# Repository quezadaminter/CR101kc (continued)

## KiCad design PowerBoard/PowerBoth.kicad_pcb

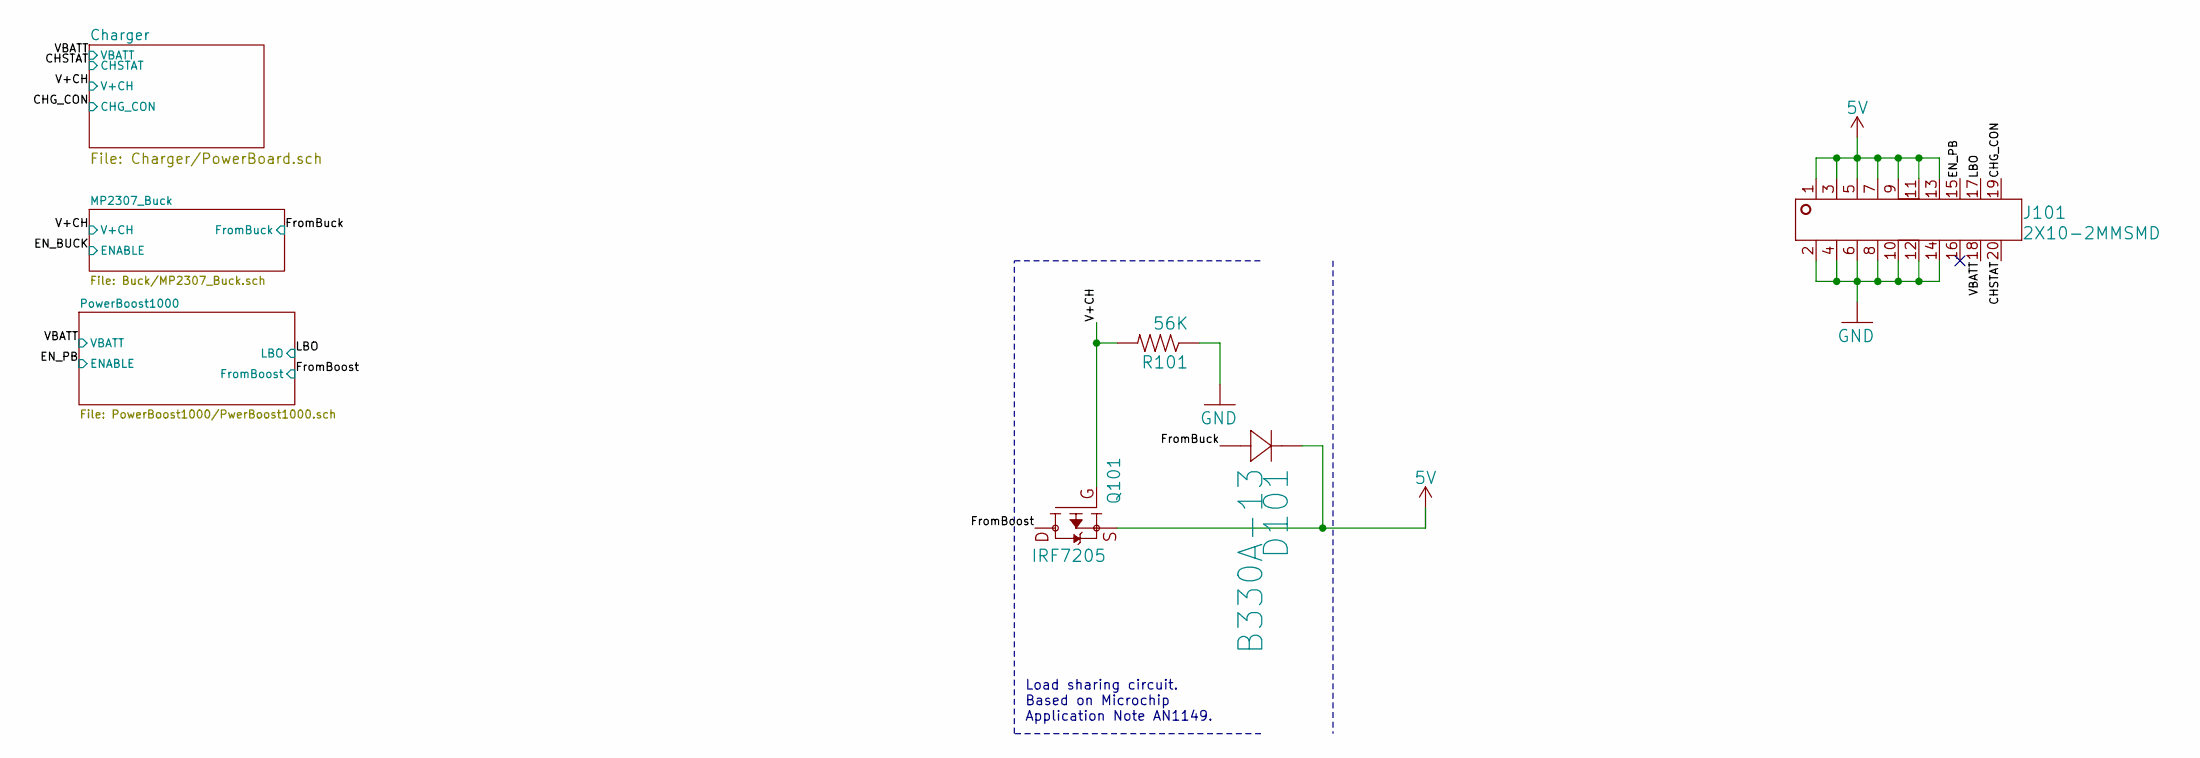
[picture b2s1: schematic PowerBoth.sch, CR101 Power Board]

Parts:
D101: B330A-13; SMA-M; DigiKey B330B-13-F
J101: 2X10-2MMSMD; 2X10-2MM; DigiKey NPPN102GFNP-RC
Q101: IRF7205; 8SOIC; LCSC Part Number C55419
R101: 56K; 1206; DigiKey CRCW120656K0FKEA

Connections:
5V: D101.1, J101.1, J101.3, J101.5, J101.7, J101.9, J101.11, J101.13, Q101.1 (S), Q101.2 (S), Q101.3 (S)
/CHG_CON: J101.19; also elsewhere on the board
/CHSTAT: J101.20; also elsewhere on the board
/EN_PB: J101.15; also elsewhere on the board
/FromBoost: Q101.5 (D), Q101.6 (D), Q101.7 (D), Q101.8 (D); also elsewhere on the board
/FromBuck: D101.2; also elsewhere on the board
/LBO: J101.17; also elsewhere on the board
/V+CH: Q101.4 (G), R101.2; also elsewhere on the board
/VBATT: J101.18; also elsewhere on the board
GND: J101.2, J101.4, J101.6, J101.8, J101.10, J101.12, J101.14, R101.1; also elsewhere on the board

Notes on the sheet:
Load sharing circuit. Based on Microchip Application Note AN1149.

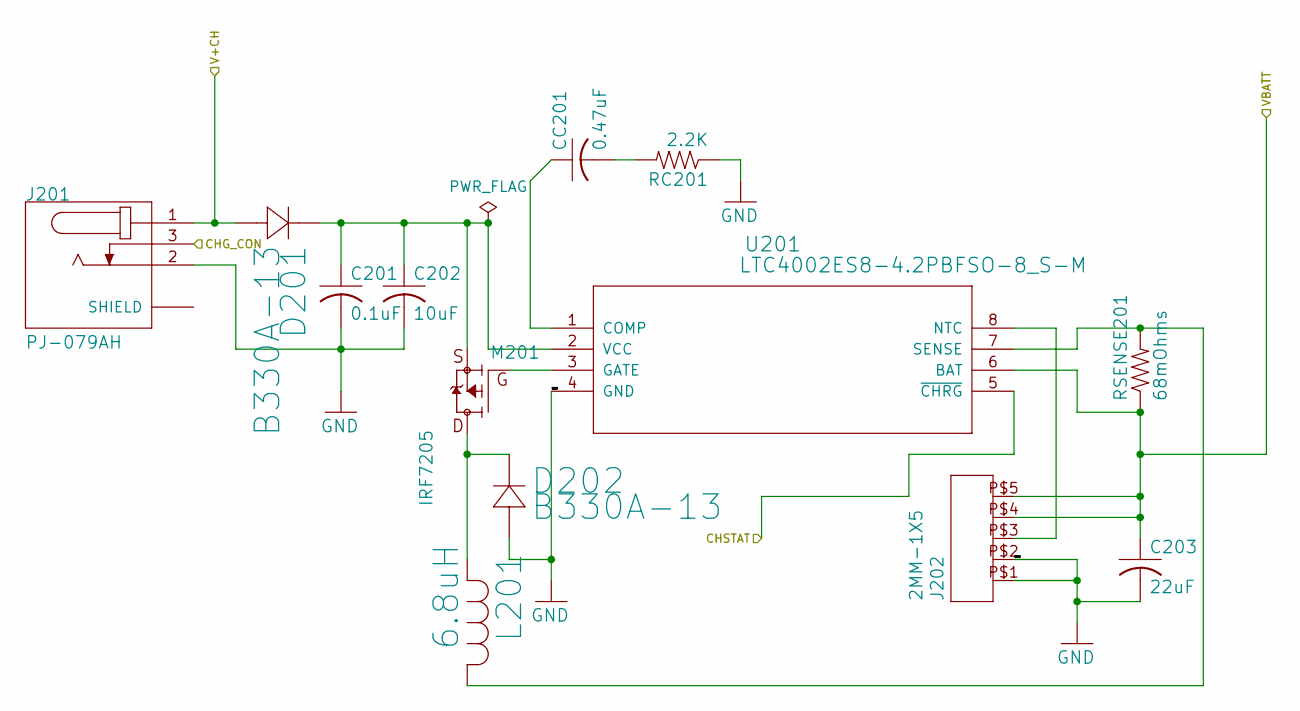
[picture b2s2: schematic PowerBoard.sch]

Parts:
C201: 0.1uF; C_0805_2012Metric_Pad1.15x1.40mm_HandSolder; LCSC Part Number C49678
C202: 10uF; C_0805_2012Metric_Pad1.15x1.40mm_HandSolder; DigiKey EMK212BB7106MG-T
C203: 22uF; C_1210_3225Metric_Pad1.42x2.65mm_HandSolder; DigiKey CL21A226MAQNNNE
CC201: 0.47uF; C_0603_1608Metric_Pad1.05x0.95mm_HandSolder; DigiKey C0805C474K3RACAUTO
D201, D202: B330A-13; SMA-M; DigiKey B330B-13-F
J201: PJ-079AH; CUI_PJ-079AH; DigiKey PJ-079AH
J202: 2MM-1X5; 2MM_1X5; DigiKey 0533250560
L201: 6.8uH; IND_B952AS-H-220M=P3; DigiKey #B952AS-H-6R8N=P3
M201: IRF7205; 8SOIC; LCSC Part Number C55419
RC201: 2.2K; R1206; DigiKey RC0805FR-072K2L
RSENSE201: 68mOhms; R1206; DigiKey KDV08FR068ET
U201: LTC4002ES8-4.2PBFSO-8_S-M; SO-8_S-M; DigiKey LTC4002ES8-4.2#TRPBF

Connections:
/CHG_CON: J201.3; also elsewhere on the board
/CHSTAT: U201.5 (~CHRG); also elsewhere on the board
/V+CH: D201.2, J201.1; also elsewhere on the board
/VBATT: C203.1, J202.P$4, J202.P$5, RSENSE201.1, U201.6 (BAT); also elsewhere on the board
GND: C201.2, C202.2, C203.2, D202.2, J201.2, J202.P$1, J202.P$2, RC201.1, U201.4 (GND); also elsewhere on the board
unnamed: C201.1, C202.1, D201.1, M201.1 (S), M201.2 (S), M201.3 (S), U201.2 (VCC)
unnamed: CC201.1, U201.1 (COMP)
unnamed: CC201.2, RC201.2
unnamed: D202.1, L201.2, M201.5 (D), M201.6 (D), M201.7 (D), M201.8 (D)
unnamed: J201.S1 (SHIELD), J201.S2 (SHIELD)
unnamed: J202.P$3, U201.8 (NTC)
unnamed: L201.1, RSENSE201.2, U201.7 (SENSE)
unnamed: M201.4 (G), U201.3 (GATE)

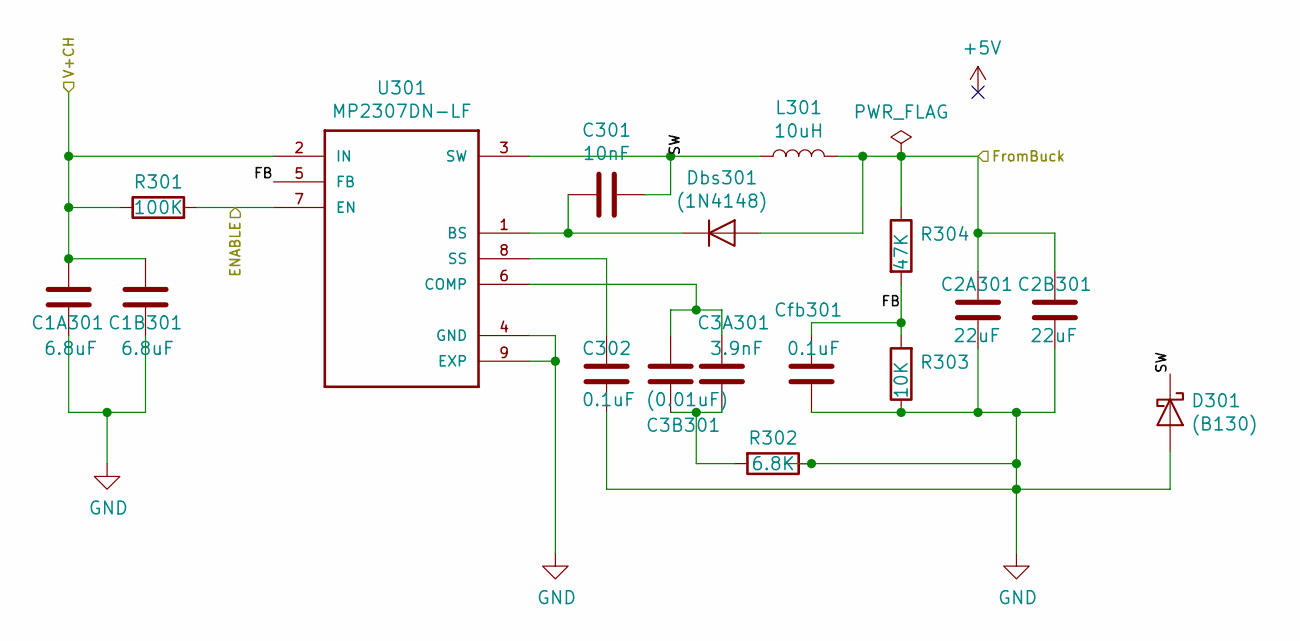
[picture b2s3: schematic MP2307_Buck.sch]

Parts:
C1A301, C1B301: 6.8uF; C_0805_2012Metric_Pad1.15x1.40mm_HandSolder; DigiKey C2012X5R1C685M085AC
C2A301, C2B301: 22uF; C_0805_2012Metric_Pad1.15x1.40mm_HandSolder; DigiKey EMK212BB7106MG-T
C3A301: 3.9nF; C_0805_2012Metric_Pad1.15x1.40mm_HandSolder; DigiKey C0805C395K8PACTU
C3B301: (0.01uF); C_0805_2012Metric_Pad1.15x1.40mm_HandSolder; DigiKey C0805C103K3RACTU
C301: 10nF; C_0805_2012Metric_Pad1.15x1.40mm_HandSolder; DigiKey C0805C104M3RACTU
C302: 0.1uF; C_0805_2012Metric_Pad1.15x1.40mm_HandSolder; DigiKey C0805C104M3RACTU
Cfb301: 0.1uF; C_0805_2012Metric_Pad1.15x1.40mm_HandSolder; DigiKey C0805C104M3RACTU
D301: (B130); D_SMB_Handsoldering; DigiKey B130LB-13-F
Dbs301: (1N4148); D_SOD-123; DigiKey 1N4148WQ-7-F
L301: 10uH; L_10.4x10.4_H4.8; DigiKey SD8350-100-R
R301: 100K; R_0805_2012Metric_Pad1.15x1.40mm_HandSolder; DigiKey RC0805FR-07100KL
R302: 6.8K; R_0805_2012Metric_Pad1.15x1.40mm_HandSolder; DigiKey CRG0805F6K8
R303: 10K; R_0805_2012Metric_Pad1.15x1.40mm_HandSolder; DigiKey RC0805FR-0710KL
R304: 47K; R_0805_2012Metric_Pad1.15x1.40mm_HandSolder; DigiKey RC0805FR-0747KL
U301: MP2307DN-LF; SOIC127P600X170-9N; DigiKey MP2307DN-LF-Z

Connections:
/EN_BUCK: R301.2, U301.7 (EN)
/FromBuck: C2A301.1, C2B301.1, Dbs301.2 (A), L301.2, R304.1; also elsewhere on the board
/MP2307_Buck/FB: Cfb301.1, R303.2, R304.2, U301.5 (FB)
/MP2307_Buck/SW: C301.1, D301.1 (K), L301.1, U301.3 (SW)
/V+CH: C1A301.1, C1B301.1, R301.1, U301.2 (IN); also elsewhere on the board
GND: C1A301.2, C1B301.2, C2A301.2, C2B301.2, C302.2, Cfb301.2, D301.2 (A), R302.1, R303.1, U301.4 (GND), U301.9 (EXP); also elsewhere on the board
unnamed: C3A301.1, C3B301.1, U301.6 (COMP)
unnamed: C3A301.2, C3B301.2, R302.2
unnamed: C301.2, Dbs301.1 (K), U301.1 (BS)
unnamed: C302.1, U301.8 (SS)

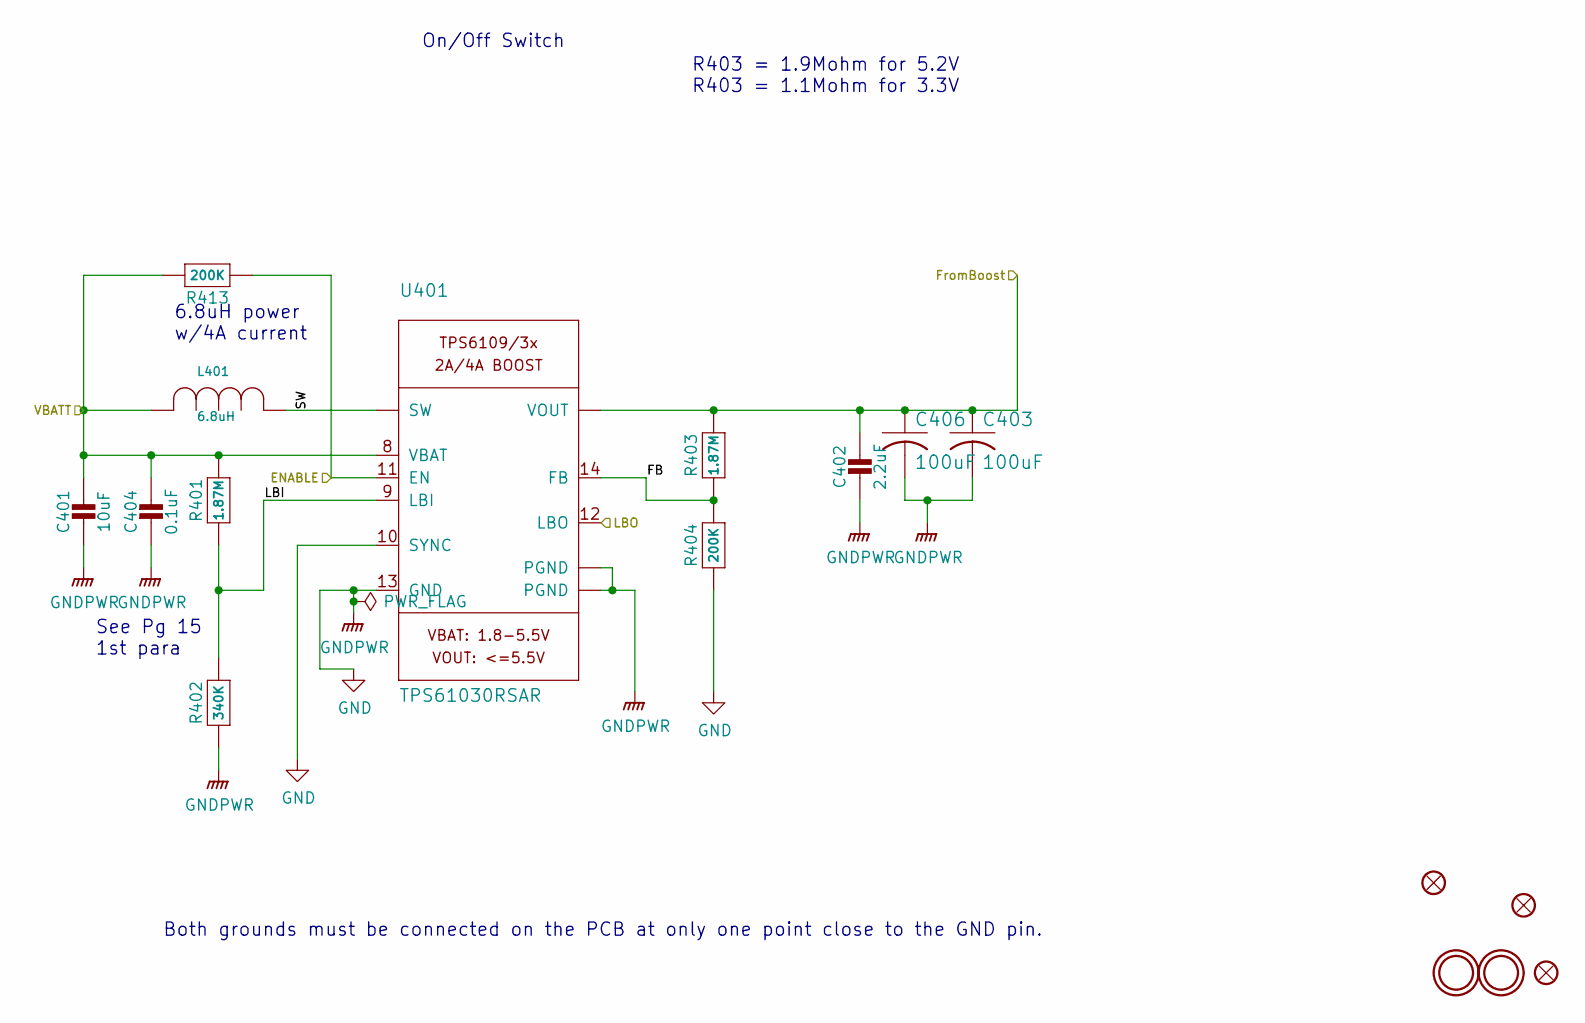
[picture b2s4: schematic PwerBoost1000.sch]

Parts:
C401: 10uF; C_0805_2012Metric_Pad1.15x1.40mm_HandSolder; DigiKey EMK212BB7106MG-T
C402: 2.2uF; C_0805_2012Metric_Pad1.15x1.40mm_HandSolder; DigiKey GRM21BR71C225KA12L
C403, C406: 100uF; C_1210_3225Metric_Pad1.42x2.65mm_HandSolder; DigiKey EMK325ABJ107MM-T
C404: 0.1uF; C_0805_2012Metric_Pad1.15x1.40mm_HandSolder; DigiKey C0805C104M3RACTU
FID401, FID402, FID403: FIDUCIAL\"\"; FIDUCIAL_1MM
L401: 6.8uH; IND_B952AS-H-220M=P3; DigiKey #B952AS-H-6R8N=P3
R401, R403: 1.87M; R_0805_2012Metric_Pad1.15x1.40mm_HandSolder; DigiKey ERJ-6ENF1874V
R402: 340K; R_0805_2012Metric_Pad1.15x1.40mm_HandSolder; DigiKey RC0805FR-07340KL
R404, R413: 200K; R_0805_2012Metric_Pad1.15x1.40mm_HandSolder; DigiKey RMCF0805FT200K
U401: TPS61030RSAR; PVQFN-16; DigiKey TPS61030RSAR
U$401, U$402: MOUNTINGHOLE2.5; MountingHole_2.5mm_Pad

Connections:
/EN_PB: R413.1, U401.11 (EN); also elsewhere on the board
/FromBoost: C402.1, C403.1, C406.1, R403.2, U401.1 (VOUT), U401.15 (VOUT), U401.16 (VOUT); also elsewhere on the board
/LBO: U401.12 (LBO); also elsewhere on the board
/PowerBoost1000/FB: R403.1, R404.2, U401.14 (FB)
/PowerBoost1000/LBI: R401.1, R402.2, U401.9 (LBI)
/PowerBoost1000/SW: L401.1, U401.3 (SW), U401.4 (SW)
/VBATT: C401.1, C404.1, L401.2, R401.2, R413.2, U401.8 (VBAT); also elsewhere on the board
GND: C401.2, C402.2, C403.2, C404.2, C406.2, R402.1, R404.1, U401.5 (PGND), U401.6 (PGND), U401.7 (PGND), U401.10 (SYNC), U401.13 (GND), U401.17 (PGND), U401.P$18 (PGND), U401.P$19 (PGND), U401.P$20 (PGND), U401.P$21 (PGND), U401.P$22 (PGND); also elsewhere on the board

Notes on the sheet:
Both grounds must be connected on the PCB at only one point close to the GND pin.
On/Off Switch
See Pg 15 1st para
6.8uH power w/4A current
R403 = 1.9Mohm for 5.2V R403 = 1.1Mohm for 3.3V

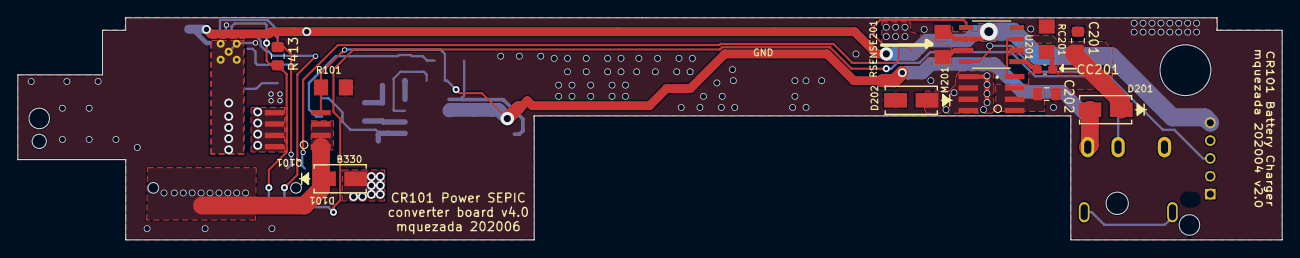
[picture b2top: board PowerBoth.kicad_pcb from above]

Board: 2 copper layers, 141.8 x 24.9 mm, 54 parts (0 on the bottom side), 28 nets.

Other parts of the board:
@HOLE0, @HOLE1, @HOLE2, @HOLE3, @HOLE4: (no value)

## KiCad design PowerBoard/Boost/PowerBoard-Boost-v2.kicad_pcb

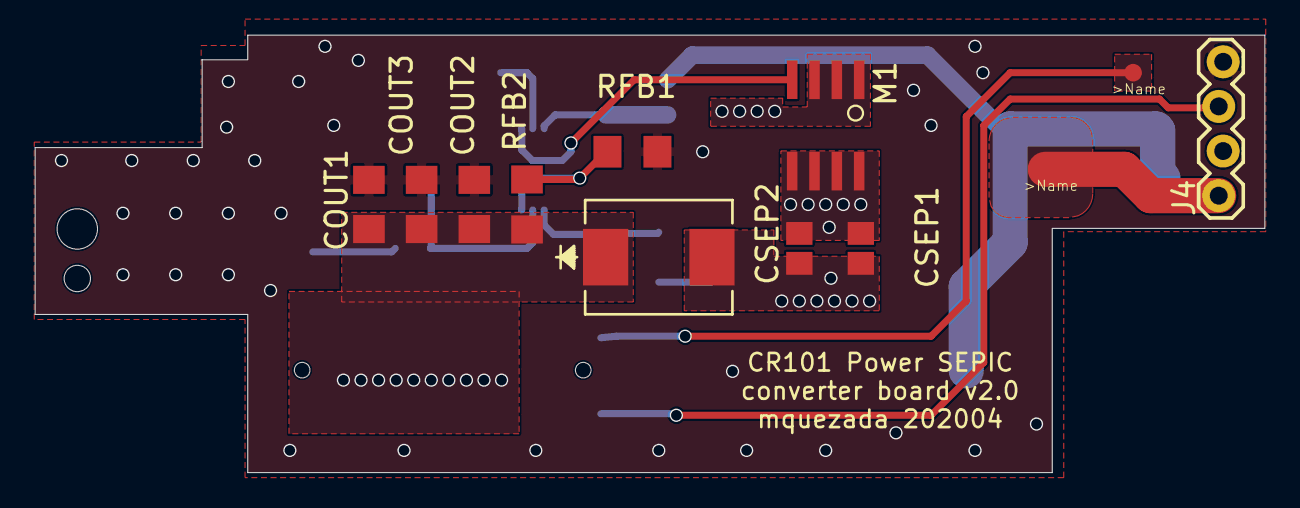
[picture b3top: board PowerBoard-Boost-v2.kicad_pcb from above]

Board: 2 copper layers, 70.0 x 24.9 mm, 28 parts (0 on the bottom side), 16 nets.

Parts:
@HOLE0, @HOLE1: (no value)
CBP1: 0.1uF; C1206
CCOMP1: 0.47uF; C1206
CCOMP2: 15nF; C0805
CFILT1: 1.5nF; C0805
CIN1, CIN2: 3.3uF; 153CLV-0505
COUT1, COUT2, COUT3: 47uF; C1206
CSEP1, CSEP2: 3.3uF; C0805
D1: SL44-E3_57TDIODE_DO214AB-M; DIODE_DO214AB-M
J1: 2X10-2MMSMD; 2X10-2MM
J4: CONN_04LOCK; 1X04_LOCK
L1: INDUCTOR_DUAL; DRQ125
M1: MOSFET_NSI4778DY; 8SOIC
RBP1: 20; R0805
RCOMP1: 215; R0805
RFADJ1: 76.8K; R0805
RFB1: 10k; R1206
RFB2: 29.4K; R1206
RFILT1: 100; R1206
RSENSE1: 0.009; R1206
TP1: Charger+; TEST_POINT_ROUND_1MM
TP2: STAT; TEST_POINT_ROUND_1MM
U1: LM3488QMM_NOPBDGK8-M; DGK8-M

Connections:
5V: COUT1.1, COUT2.1, COUT3.1, D1.1, J1.1, J1.3, J1.5, J1.7, J1.9, J1.11, J1.13, RFB2.2
/PowerBoard-Boost-v2_1/BB: CIN1.+, CIN2.+, J4.2, L1.1, RBP1.2
/PowerBoard-Boost-v2_1/COMP: CCOMP2.1, RCOMP1.2, U1.2
/PowerBoard-Boost-v2_1/DR: M1.4, U1.6
/PowerBoard-Boost-v2_1/FA: RFADJ1.2, U1.7
/PowerBoard-Boost-v2_1/FB: RFB1.2, RFB2.1, U1.3
/PowerBoard-Boost-v2_1/ISEN: CFILT1.1, RFILT1.2, U1.1
/PowerBoard-Boost-v2_1/SOURCE: M1.1, M1.2, M1.3, RFILT1.1, RSENSE1.2
/PowerBoard-Boost-v2_1/STAT: J1.20, TP2.1
/PowerBoard-Boost-v2_1/VCC_SENSE: J1.19, J4.3
/PowerBoard-Boost-v2_1/VIN: CBP1.1, RBP1.1, U1.8
/PowerBoard-Boost-v2_1/VIN3: CSEP1.2, CSEP2.2, L1.3, M1.5, M1.6, M1.7, M1.8
/PowerBoard-Boost-v2_1/VOUT: CSEP1.1, CSEP2.1, D1.2, L1.2
GND: CBP1.2, CCOMP1.2, CCOMP2.2, CFILT1.2, CIN1.-, CIN2.-, COUT1.2, COUT2.2, COUT3.2, J1.2, J1.4, J1.6, J1.8, J1.10, J1.12, J1.14, J1.16, J4.4, L1.4, RFADJ1.1, RFB1.1, RSENSE1.1, U1.4, U1.5
unnamed: CCOMP1.1, RCOMP1.1
VCC: J4.1, TP1.1

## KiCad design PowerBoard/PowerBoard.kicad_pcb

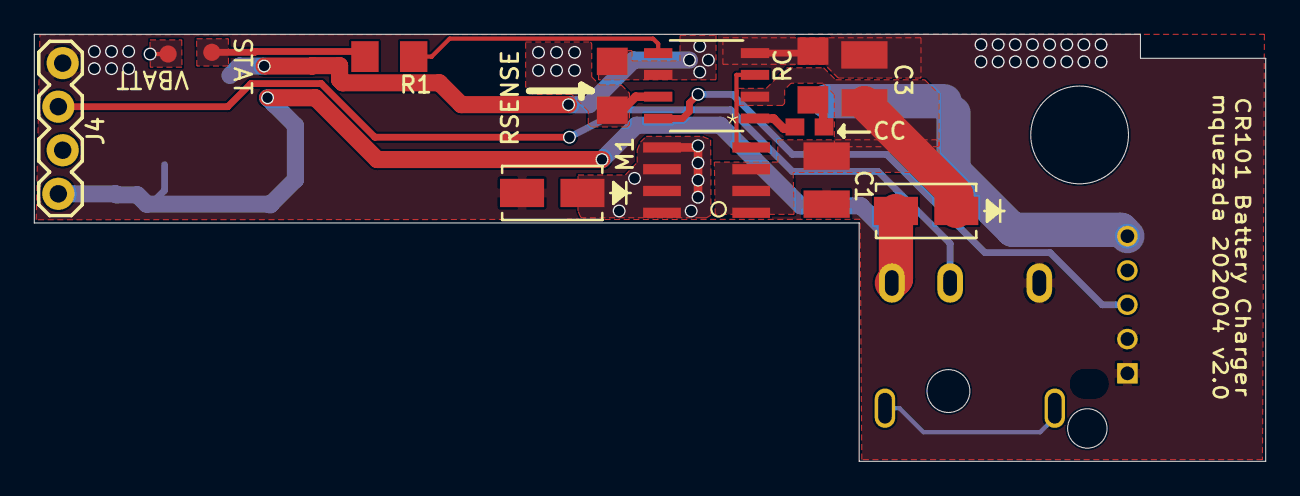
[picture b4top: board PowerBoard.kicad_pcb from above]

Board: 2 copper layers, 71.8 x 24.9 mm, 23 parts (0 on the bottom side), 15 nets.

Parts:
@HOLE0, @HOLE1, @HOLE2: (no value)
C1: 10uF; C1210
C2: 22uF; C1210
C3: 0.1uF; C1210
CC: 0.47uF; C0603
D1, D2, D3: B330A-13; SMA-M
J1: 2MM-1X5; 2MM_1X5
J2: PJ-079AH; CUI_PJ-079AH
J4: CONN_04LOCK; 1X04_LOCK
L1: 6.8uH; IND_B952AS-H-220M=P3
M1: IRF7205; 8SOIC
Q10: IRF7205; 8SOIC
R1: 2K; R1206
R47: 56K; 1206
RC: R-US_R1206; R1206
RSENSE: 68mOhms; R1206
TP1-STAT101: TEST_POINTROUND-1MM; TEST_POINT_ROUND_1MM
U1: LTC4002ES8-4.2PBFSO-8_S-M; SO-8_S-M
VBATT: TEST_POINTROUND-1MM; TEST_POINT_ROUND_1MM

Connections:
/STAT: R1.2, TP1-STAT101.1
/VCC_SENSE: J2.3, J4.3
GND: C1.2, C2.2, C3.2, D2.2, J1.P$1, J1.P$2, J2.2, J4.4, R47.1, RC.1, U1.4
unnamed: C1.1, C3.1, D1.1, M1.1, M1.2, M1.3, U1.2
unnamed: CC.1, U1.1
unnamed: CC.2, RC.2
unnamed: D2.1, L1.2, M1.5, M1.6, M1.7, M1.8
unnamed: D3.1, J4.2, Q10.1, Q10.2, Q10.3
unnamed: J1.P$3, U1.8
unnamed: J2.S1, J2.S2
unnamed: L1.1, RSENSE.2, U1.7
unnamed: M1.4, U1.3
unnamed: R1.1, U1.5
VCC: D1.2, D3.2, J2.1, J4.1, Q10.4, R47.2
V_BATT: C2.1, J1.P$4, J1.P$5, Q10.5, Q10.6, Q10.7, Q10.8, RSENSE.1, U1.6, VBATT.1

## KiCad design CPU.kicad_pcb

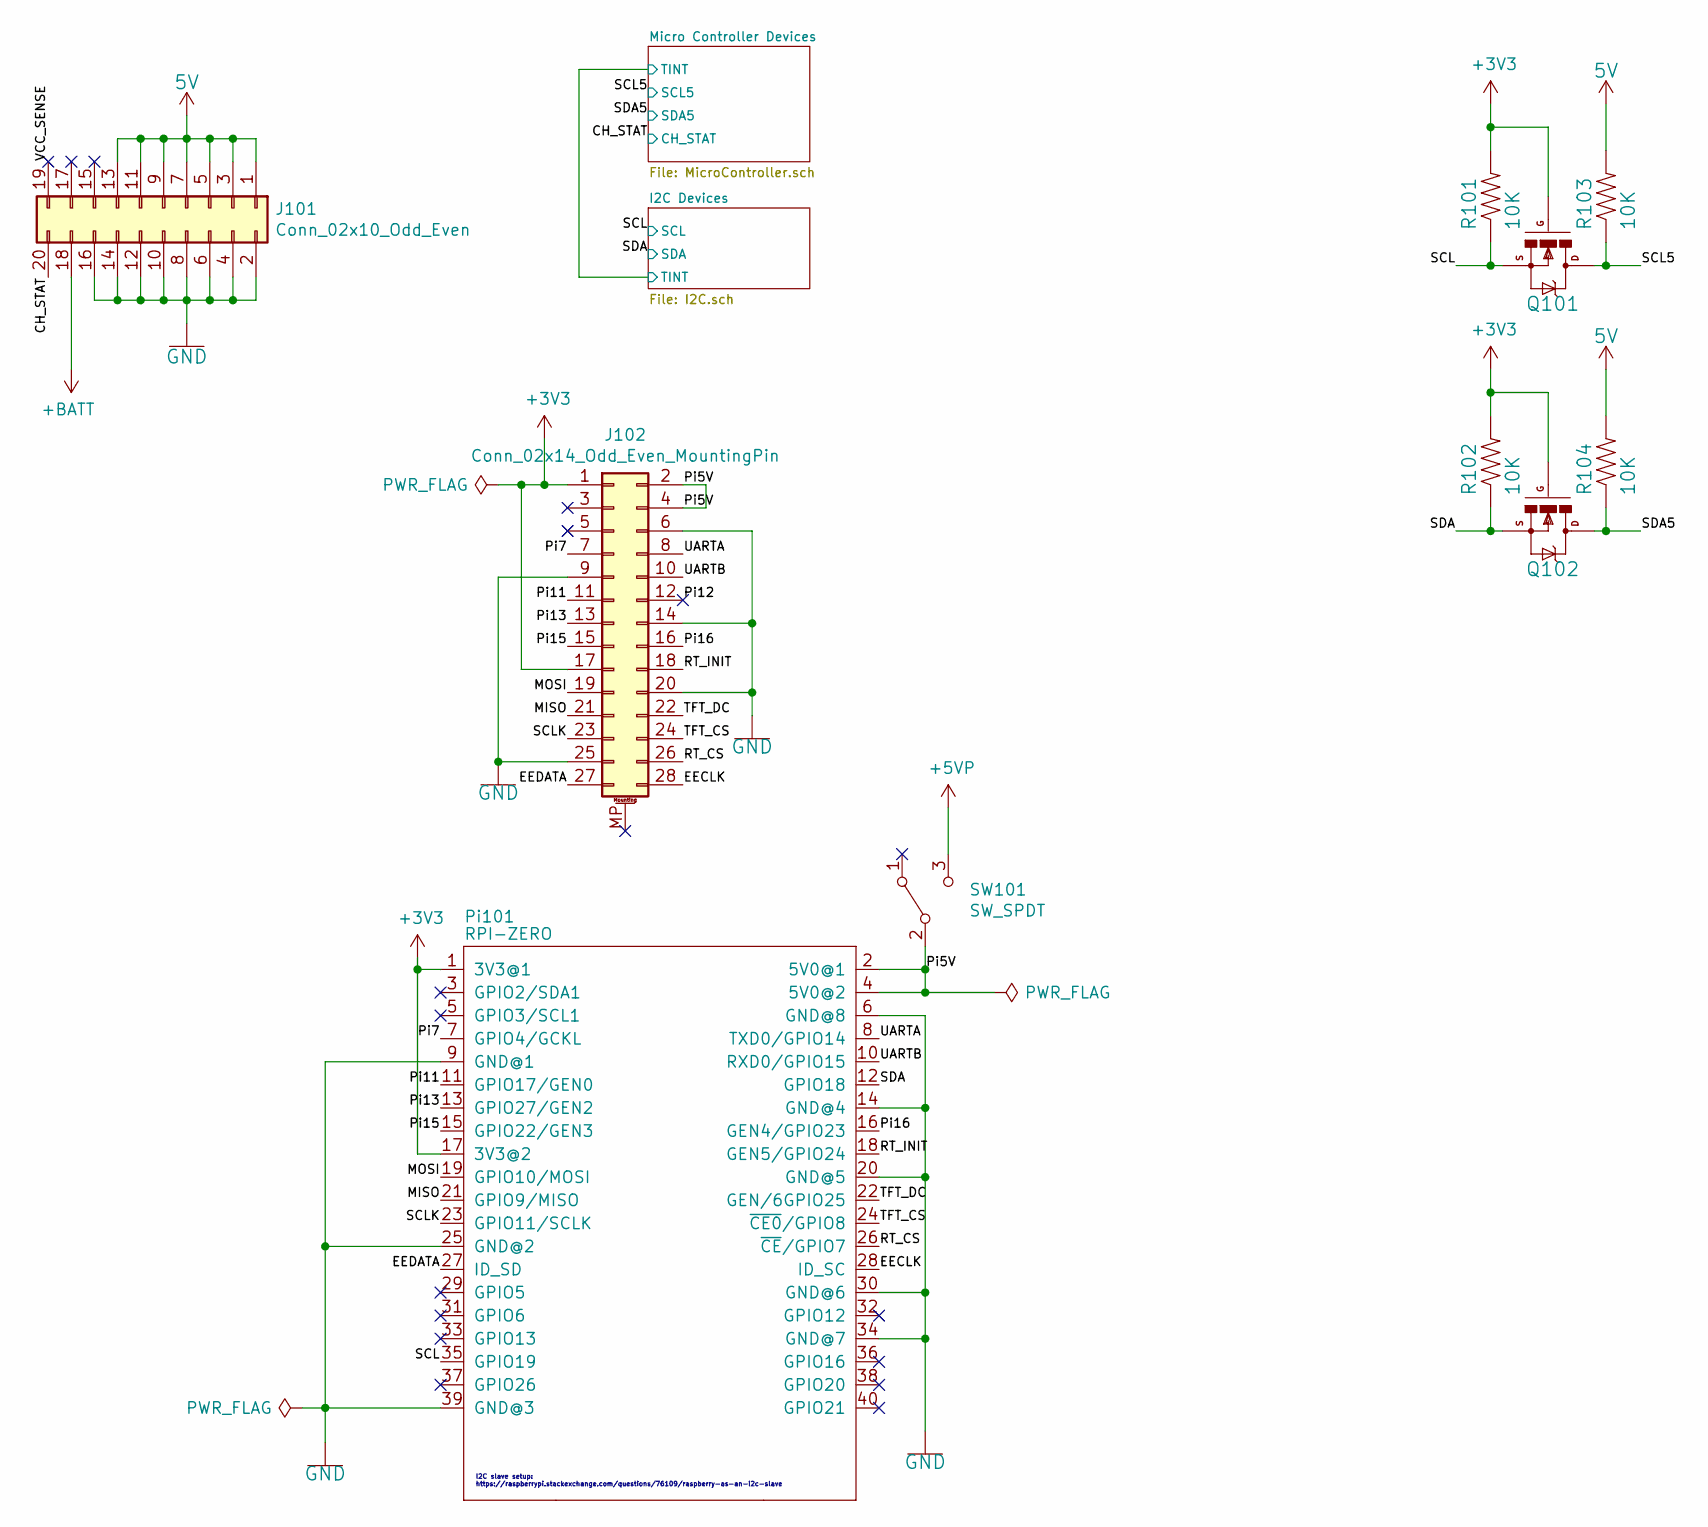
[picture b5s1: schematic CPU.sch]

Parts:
J101: Conn_02x10_Odd_Even; PinHeader_2x10_P2.00mm_Vertical_SMD; LCSC Part Number C135211
J102: Conn_02x14_Odd_Even_MountingPin; 2X14_SMT_MALE-2
Pi101: RPI-ZERO; RASPBERRYPI_Zero-No_Mounting_Holes
Q101, Q102: IRLML0040TR; SOT23; LCSC Part Number C67273
R101, R102, R103, R104: 10K; R1206; LCSC Part Number C17902
SW101: SW_SPDT; SWITCH_PCM12SMTR_SPDT; LCSC Part Number C221841

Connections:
5V: J101.1, J101.3, J101.5, J101.7, J101.9, J101.11, J101.13, R103.2, R104.2; also elsewhere on the board
+3V3: J102.1, J102.17, Pi101.1 (3V3@1), Pi101.17 (3V3@2), Q101.1 (G), Q102.1 (G), R101.2, R102.2; also elsewhere on the board
+5VP: SW101.3 (C); also elsewhere on the board
+BATT: J101.18; also elsewhere on the board
/CH_STAT: J101.20; also elsewhere on the board
/EECLK: J102.28, Pi101.28 (ID_SC)
/EEDATA: J102.27, Pi101.27 (ID_SD)
/MISO: J102.21, Pi101.21 (GPIO9/MISO)
/MOSI: J102.19, Pi101.19 (GPIO10/MOSI)
/Pi5V: J102.2, J102.4, Pi101.2 (5V0@1), Pi101.4 (5V0@2), SW101.2 (B)
/Pi7: J102.7, Pi101.7 (GPIO4/GCKL)
/Pi11: J102.11, Pi101.11 (GPIO17/GEN0)
/Pi12: J102.12
/Pi13: J102.13, Pi101.13 (GPIO27/GEN2)
/Pi15: J102.15, Pi101.15 (GPIO22/GEN3)
/Pi16: J102.16, Pi101.16 (GEN4/GPIO23)
/RT_CS: J102.26, Pi101.26 (~CE~/GPIO7)
/RT_INIT: J102.18, Pi101.18 (GEN5/GPIO24)
/SCL: Pi101.35 (GPIO19), Q101.2 (S), R101.1; also elsewhere on the board
/SCL5: Q101.3 (D), R103.1; also elsewhere on the board
/SCLK: J102.23, Pi101.23 (GPIO11/SCLK)
/SDA: Pi101.12 (GPIO18), Q102.2 (S), R102.1; also elsewhere on the board
/SDA5: Q102.3 (D), R104.1; also elsewhere on the board
/TFT_CS: J102.24, Pi101.24 (~CE0~/GPIO8)
/TFT_DC: J102.22, Pi101.22 (GEN/6GPIO25)
/UARTA: J102.8, Pi101.8 (TXD0/GPIO14)
/UARTB: J102.10, Pi101.10 (RXD0/GPIO15)
/VCC_SENSE: J101.19
GND: J101.2, J101.4, J101.6, J101.8, J101.10, J101.12, J101.14, J101.16, J102.6, J102.9, J102.14, J102.20, J102.25, Pi101.6 (GND@8), Pi101.9 (GND@1), Pi101.14 (GND@4), Pi101.20 (GND@5), Pi101.25 (GND@2), Pi101.30 (GND@6), Pi101.34 (GND@7), Pi101.39 (GND@3); also elsewhere on the board

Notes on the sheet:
I2C slave setup: https://raspberrypi.stackexchange.com/questions/76109/raspberry-as-an-i2c-slave

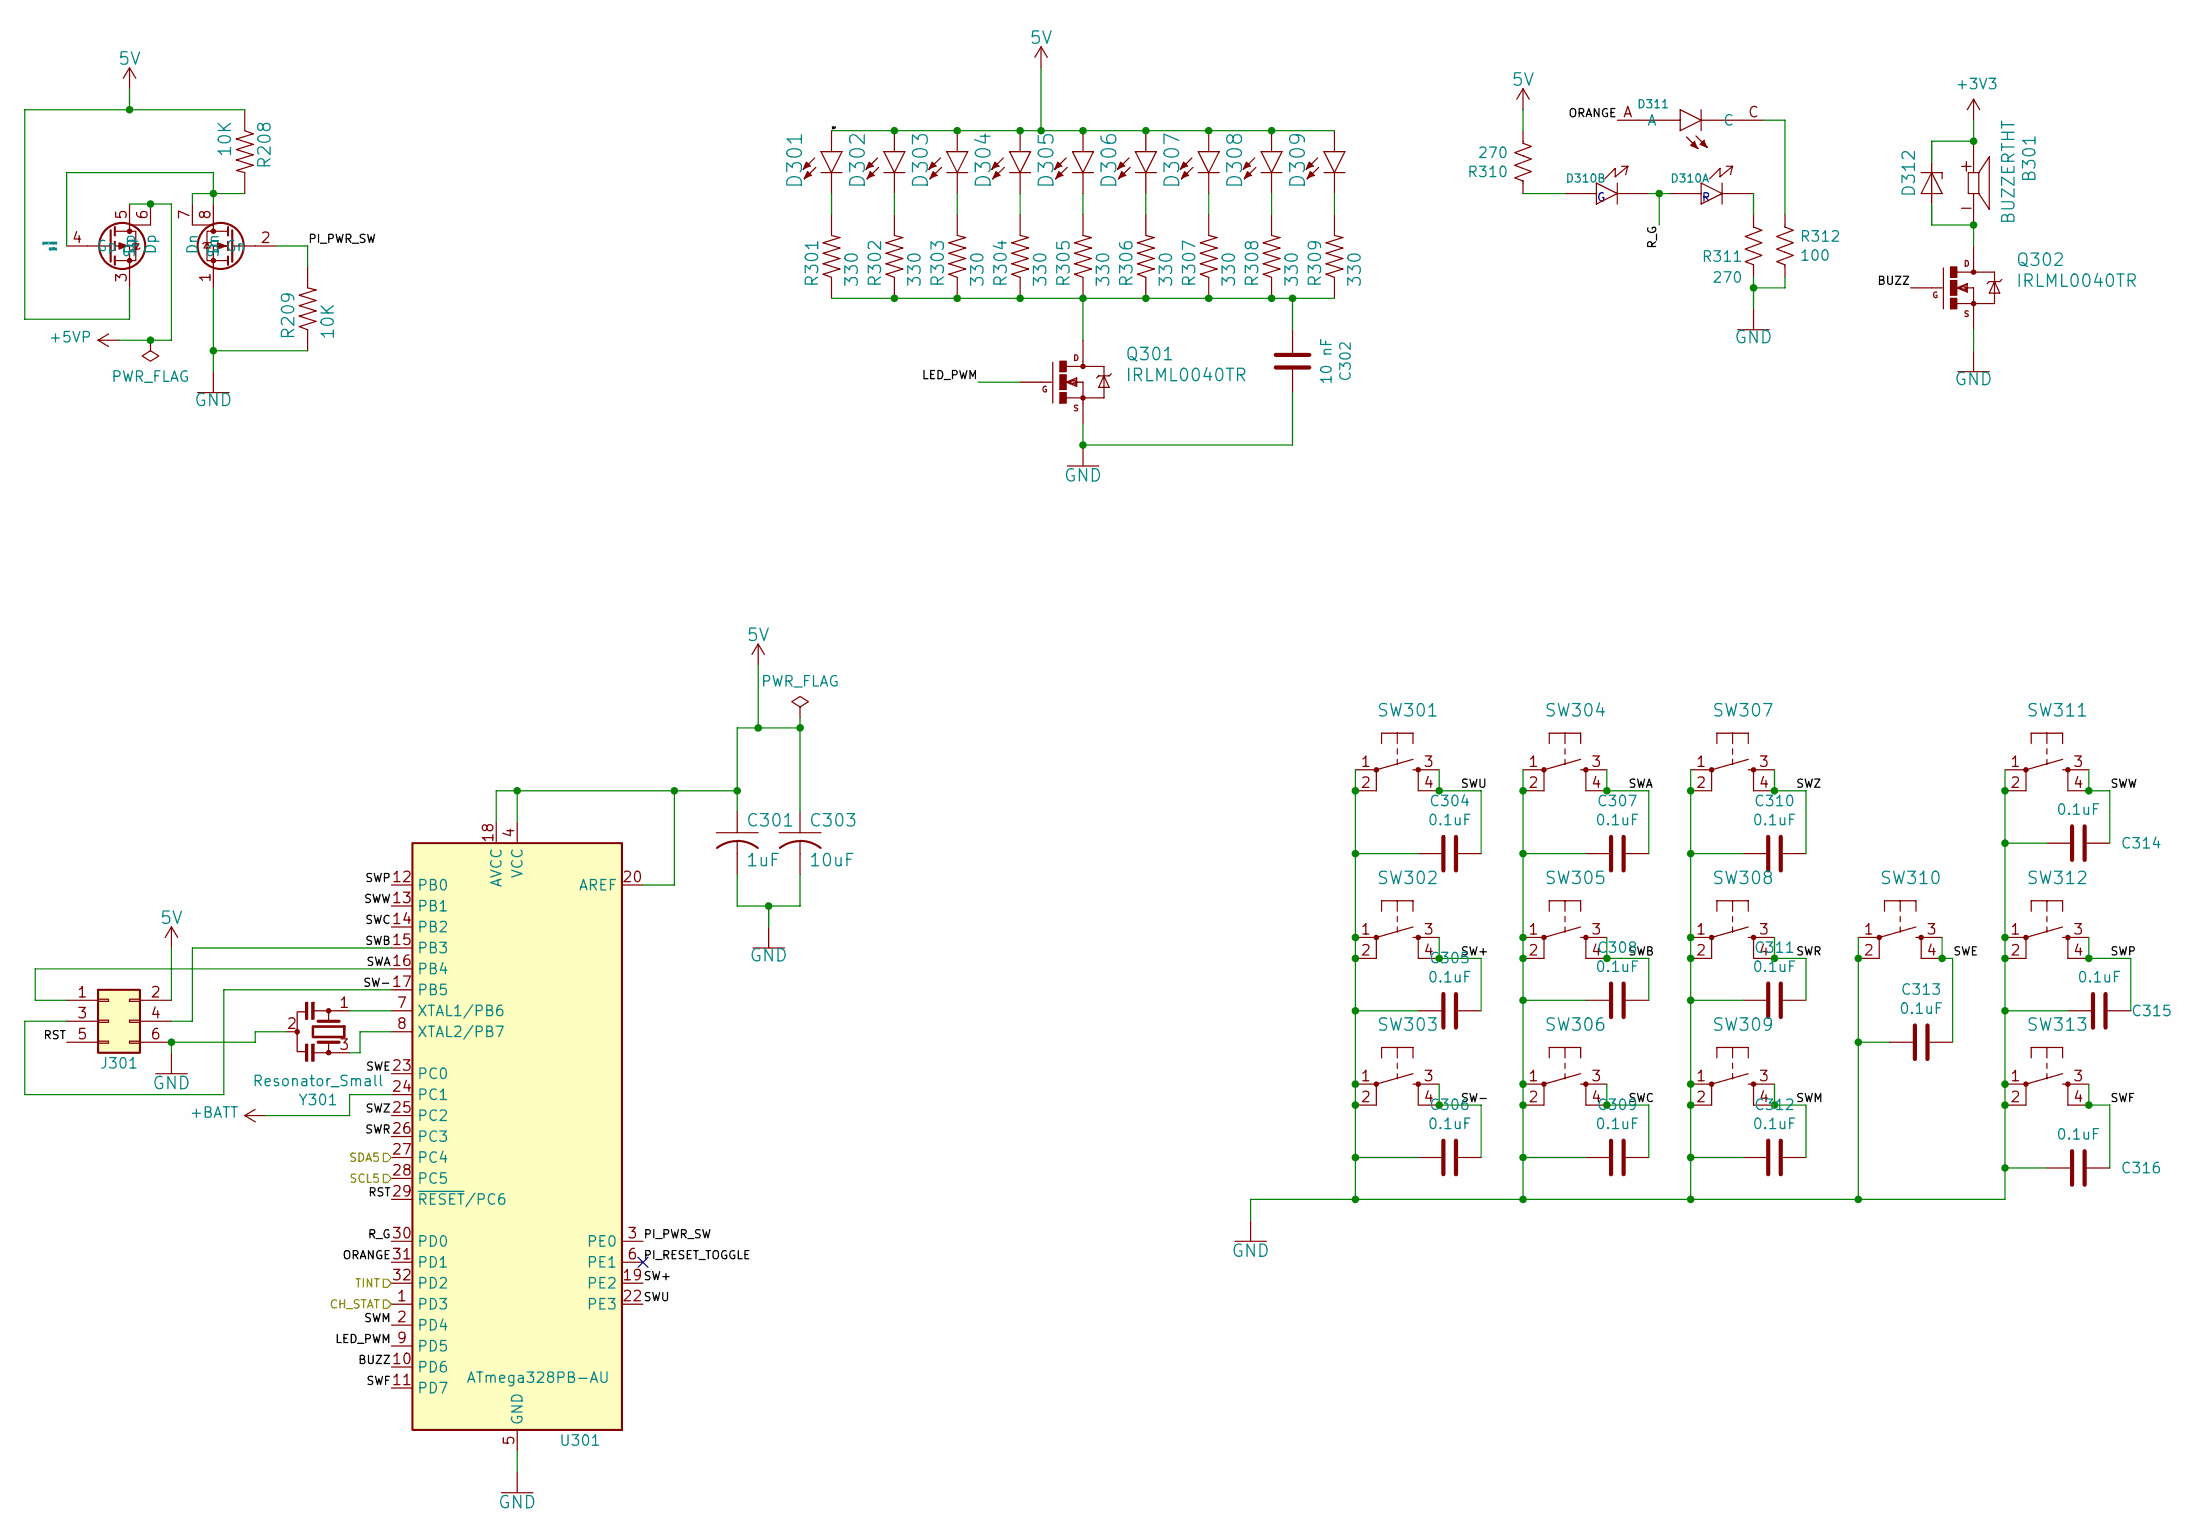
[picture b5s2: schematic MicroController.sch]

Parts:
B301: BUZZERTHT; XDCR_CMT-0904-85T; DigiKey CMT-0904-85T
C301: 1uF; C1210; LCSC Part Number C1848
C302: 10 nF; C_0805_2012Metric_Pad1.15x1.40mm_HandSolder; LCSC Part Number C1710
C303: 10uF; C1210; LCSC Part Number C13585
C304, C305, C306, C307, C308, C309, C310, C311, C312, C313, C314, C315, C316: 0.1uF; C_0805_2012Metric_Pad1.15x1.40mm_HandSolder; LCSC Part Number C49678
D301, D302, D303, D304, D305, D306, D307, D308, D309: LED0603; LED-0603; LCSC Part Number C161619
D310: RG; INOLUX_IN-S85DATRG; LCSC Part Number C391863
D311: 598-8030-107F; LEDSC160X80X70L45N; LCSC Part Number C264422
D312: DIODE; MICRO_SMP; LCSC Part Number C111315
J301: Conn_02x03_Odd_Even; PinHeader_2x03_P2.54mm_Vertical; DigiKey 818-22-006-10-002101, 818-22-006-10-005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
Q201: DMC4050; 8-SMD; DigiKey DMC4050SSD-13
Q301, Q302: IRLML0040TR; SOT23; LCSC Part Number C67273
R208, R209: 10K; R1206; LCSC Part Number C17902
R301, R302, R303, R304, R305, R306, R307, R308, R309: 330; R1206; LCSC Part Number C17930
R310, R311: 270; R_0805_2012Metric_Pad1.15x1.40mm_HandSolder; LCSC Part Number C17590
R312: 100; R_0805_2012Metric_Pad1.15x1.40mm_HandSolder; LCSC Part Number C17408
SW301, SW302, SW303, SW304, SW305, SW306, SW307, SW308, SW309, SW310, SW311, SW312, SW313: TACTILE_SWITCHPTS540-SMD; PTS540-ULTRA_LOW_PROFILE_SW_SPST; LCSC Part Number C221864
U301: ATmega328PB-AU; TQFP-32_7x7mm_P0.8mm
Y301: Resonator_Small; Resonator-3Pin_W7.0mm_H2.5mm; DigiKey CSTNE20M0VH3L000R0

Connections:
5V: C301.1, C303.1, D301.A, D302.A, D303.A, D304.A, D305.A, D306.A, D307.A, D308.A, D309.A, J301.2, Q201.3 (Sp), R208.1, R310.2, U301.4 (VCC), U301.18 (AVCC), U301.20 (AREF); also elsewhere on the board
+3V3: B301.P, D312.K (C); also elsewhere on the board
+5VP: Q201.5 (Dp), Q201.6 (Dp); also elsewhere on the board
+BATT: U301.24 (PC1); also elsewhere on the board
/CH_STAT: U301.1 (PD3); also elsewhere on the board
/I2C Devices/TINT: U301.32 (PD2); also elsewhere on the board
/Micro Controller Devices/BUZZ: Q302.1 (G), U301.10 (PD6)
/Micro Controller Devices/LED_PWM: Q301.1 (G), U301.9 (PD5)
/Micro Controller Devices/ORANGE: D311.A, U301.31 (PD1)
/Micro Controller Devices/PI_PWR_SW: Q201.2 (Gn), R209.2, U301.3 (PE0)
/Micro Controller Devices/PI_RESET_TOGGLE: U301.6 (PE1)
/Micro Controller Devices/RST: J301.5, U301.29 (~RESET~/PC6)
/Micro Controller Devices/R_G: D310.1 (K), D310.4 (A), U301.30 (PD0)
/Micro Controller Devices/SW+: C305.2, SW302.3, SW302.4, U301.19 (PE2)
/Micro Controller Devices/SW-: C306.2, J301.3, SW303.3, SW303.4, U301.17 (PB5)
/Micro Controller Devices/SWA: C307.2, J301.1, SW304.3, SW304.4, U301.16 (PB4)
/Micro Controller Devices/SWB: C308.2, J301.4, SW305.3, SW305.4, U301.15 (PB3)
/Micro Controller Devices/SWC: C309.2, SW306.3, SW306.4, U301.14 (PB2)
/Micro Controller Devices/SWE: C313.2, SW310.3, SW310.4, U301.23 (PC0)
/Micro Controller Devices/SWF: C316.2, SW313.3, SW313.4, U301.11 (PD7)
/Micro Controller Devices/SWM: C312.2, SW309.3, SW309.4, U301.2 (PD4)
/Micro Controller Devices/SWP: C315.2, SW312.3, SW312.4, U301.12 (PB0)
/Micro Controller Devices/SWR: C311.2, SW308.3, SW308.4, U301.26 (PC3)
/Micro Controller Devices/SWU: C304.2, SW301.3, SW301.4, U301.22 (PE3)
/Micro Controller Devices/SWW: C314.2, SW311.3, SW311.4, U301.13 (PB1)
/Micro Controller Devices/SWZ: C310.2, SW307.3, SW307.4, U301.25 (PC2)
/SCL5: U301.28 (PC5); also elsewhere on the board
/SDA5: U301.27 (PC4); also elsewhere on the board
GND: C301.2, C302.2, C303.2, C304.1, C305.1, C306.1, C307.1, C308.1, C309.1, C310.1, C311.1, C312.1, C313.1, C314.1, C315.1, C316.1, J301.6, Q201.1 (Sn), Q301.2 (S), Q302.2 (S), R209.1, R311.2, R312.2, SW301.1, SW301.2, SW302.1, SW302.2, SW303.1, SW303.2, SW304.1, SW304.2, SW305.1, SW305.2, SW306.1, SW306.2, SW307.1, SW307.2, SW308.1, SW308.2, SW309.1, SW309.2, SW310.1, SW310.2, SW311.1, SW311.2, SW312.1, SW312.2, SW313.1, SW313.2, U301.5 (GND), U301.21 (GND), Y301.2; also elsewhere on the board
unnamed: B301.N, D312.A, Q302.3 (D)
unnamed: C302.1, Q301.3 (D), R301.1, R302.1, R303.1, R304.1, R305.1, R306.1, R307.1, R308.1, R309.1
unnamed: D301.C, R301.2
unnamed: D302.C, R302.2
unnamed: D303.C, R303.2
unnamed: D304.C, R304.2
unnamed: D305.C, R305.2
unnamed: D306.C, R306.2
unnamed: D307.C, R307.2
unnamed: D308.C, R308.2
unnamed: D309.C, R309.2
unnamed: D310.2 (A), R310.1
unnamed: D310.3 (K), R311.1
unnamed: D311.C, R312.1
unnamed: Q201.4 (Gp), Q201.7 (Dn), Q201.8 (Dn), R208.2
unnamed: U301.7 (XTAL1/PB6), Y301.1
unnamed: U301.8 (XTAL2/PB7), Y301.3
